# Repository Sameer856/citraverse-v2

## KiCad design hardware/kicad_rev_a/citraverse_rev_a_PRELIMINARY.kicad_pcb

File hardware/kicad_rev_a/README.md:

# Citraverse Rev A — preliminary KiCad interface and placement project

This is an editable KiCad 10 starting project based on the user's circular-board sketch. It is **not a fabrication-ready PCB**: there are no routed traces or implemented regulator/load-switch circuits. The board is now an 80 mm diameter placement to provide clearance for the full-size microSD socket, ESP32 antenna, radar, USB-C, microphone, speaker connector, and factory pads.

Open `citraverse_rev_a_PRELIMINARY.kicad_pro` in KiCad, then open its PCB or schematic. `preview/pcb-placement.png` and `preview/schematic.png` provide views without needing KiCad. The main project contains four copper layers and a 1.6 mm nominal thickness; stack-up and controlled-impedance requirements remain to be agreed with the fabricator.

## Implemented for review

- ESP32-S3-WROOM-1 footprint at the upper edge with antenna overhang and an all-copper-layer keepout reservation. The module pad numbering is sourced from the installed KiCad official ESP32-S3-WROOM-1 symbol. GPIO35–37 are not allocated on the N16R8.
- Centered MRS6240-P2512 footprint derived from the supplied guide's Figure 7-2: 12.00 × 25.00 mm body, 16 plated-through holes in two rows, 1.27 mm pitch, 0.90 × 2.15 mm pads, and 0.65 mm drill. The schematic records the 16 pin names/numbers. Check it against the physical purchased module before ordering any PCB.
- Left microSD socket, proposed Hirose DM3AT-SF-PEJM5 footprint, on its independent SPI bus. The card-detect contacts 9/10 are reserved and not yet used; the shield is `SH`.
- Right HRO TYPE-C-31-M-12 USB-C connector, native USB signal nets and separate 5.1 kΩ CC resistors. Connector sourcing and mechanical fit require confirmation.
- Common six-pin INMP441 breakout-module connector: VDD, GND, L/R, SD, WS, SCK. It retains the 100 nF local VDD bypass, 1 uF bulk bypass, 100 kΩ SD pulldown, and L/R grounded for left-channel operation. Verify the purchased module's printed header order before assembly; inexpensive breakouts occasionally change silkscreen order.
- MAX98357A I2S Class-D amplifier footprint and a two-pin JST-PH speaker connector. The speaker connector is differential (`SPK+`, `SPK-`); neither pin is ground.
- ESP enable pull-up/RC, service boot pull-up, local bypass placeholders and factory recovery connector.
- Four M2.5 mounting-hole candidates. Their placement must be reconciled with the enclosure, acoustic opening and antenna field of view.
- Native schematic connectivity and PCB net names, exported netlist, machine-readable pin contract and a reproducible generation script.

UART nets are explicitly named at the radar-module end: ESP GPIO18 drives `RADAR_RX_AT_MODULE` / radar PB1; ESP GPIO21 receives `RADAR_TX_AT_MODULE` / radar PB0. Radar SPI is reserved on GPIO10/12/11/13, optional lines 9/14; SD SPI is GPIO4/5/7/6; microphone I2S is GPIO15/16/17. GPIO8 is reserved for radar power enable. GPIO47 is only a PA11 reservation; it is not a confirmed data-ready signal.

## Work still required before a working board

1. Check the guide-derived MRS6240-P2512 and INMP441 footprints against physical parts. Confirm SPI role, electrical levels, reset timing, boot requirements and PA11/PA6 behavior with the dev kit/application firmware.
2. Replace `PS1` with a completed, reviewed USB-C power tree: input fuse and TVS, reverse-current protection, a 5 V protected rail for the speaker amplifier, a 3.3 V / 3 A buck for ESP32/SD/mic, and a separately switched 3.3 V radar rail. Prevent back-powering the unpowered radar through its signal pins.
3. Complete the native USB CDC factory-recovery circuit: USB ESD protection, 22 Ω D+/D- series resistors, EN/BOOT reset network, and labelled six-pad factory pogo access for 3V3/GND/EN/BOOT/UART TX/UART RX. A CH340/CP2102 bridge is deliberately not yet placed; native ESP32-S3 USB is the preferred primary factory/OTA path.
4. Complete SD pull-ups, radar series links/decoupling/reset network, USB protection and signal conditioning, status LED and temperature sensing. `STATUS_LED` and `BOARD_NTC` are only reserved MCU nets today.
5. Finalize purchased part numbers; review schematic electrical rules, pin directions and unconnected pins. The current custom block symbols are interface documentation, not a complete electrical schematic. Abstract power/radar pin types cannot validate electrical safety.
6. Keep the 80 mm round PCB, or redesign the SD location before attempting a 70 mm version. Then route the complete board, plan return paths and power planes, verify radio/microphone keepouts and USB geometry, then pass native ERC/DRC and manually review manufacturing outputs. No fabrication files have been generated.
7. Assemble and measure current, transients, heat and data throughput; complete the previously agreed combined-load and fault-injection tests.

## Validation performed

KiCad 10.0.3 successfully loaded and exported the PCB to SVG, and loaded/exported the schematic to SVG and a connectivity netlist. Both previews were visually inspected. The preliminary project has zero routed tracks by design. The KiCad command-line PCB DRC process aborted with exit 134 in this environment and did not produce a DRC report; **no DRC pass is claimed**. The host also emits font-cache warnings during schematic export, but generates the output files.

The generator overwrites these generated project files. After manual KiCad editing, preserve the edited project before re-running it. Run using KiCad's bundled Python, which supplies `pcbnew`:

```sh
/Applications/KiCad/KiCad.app/Contents/Frameworks/Python.framework/Versions/3.9/bin/python3 hardware/kicad_rev_a/build_preliminary.py
```

The reference drawing is the user's `IMG_9340.HEIC`. Design context is in the existing project architecture, module-review and ESP32 reliability documents. Their unresolved module/interface assumptions remain unresolved here.

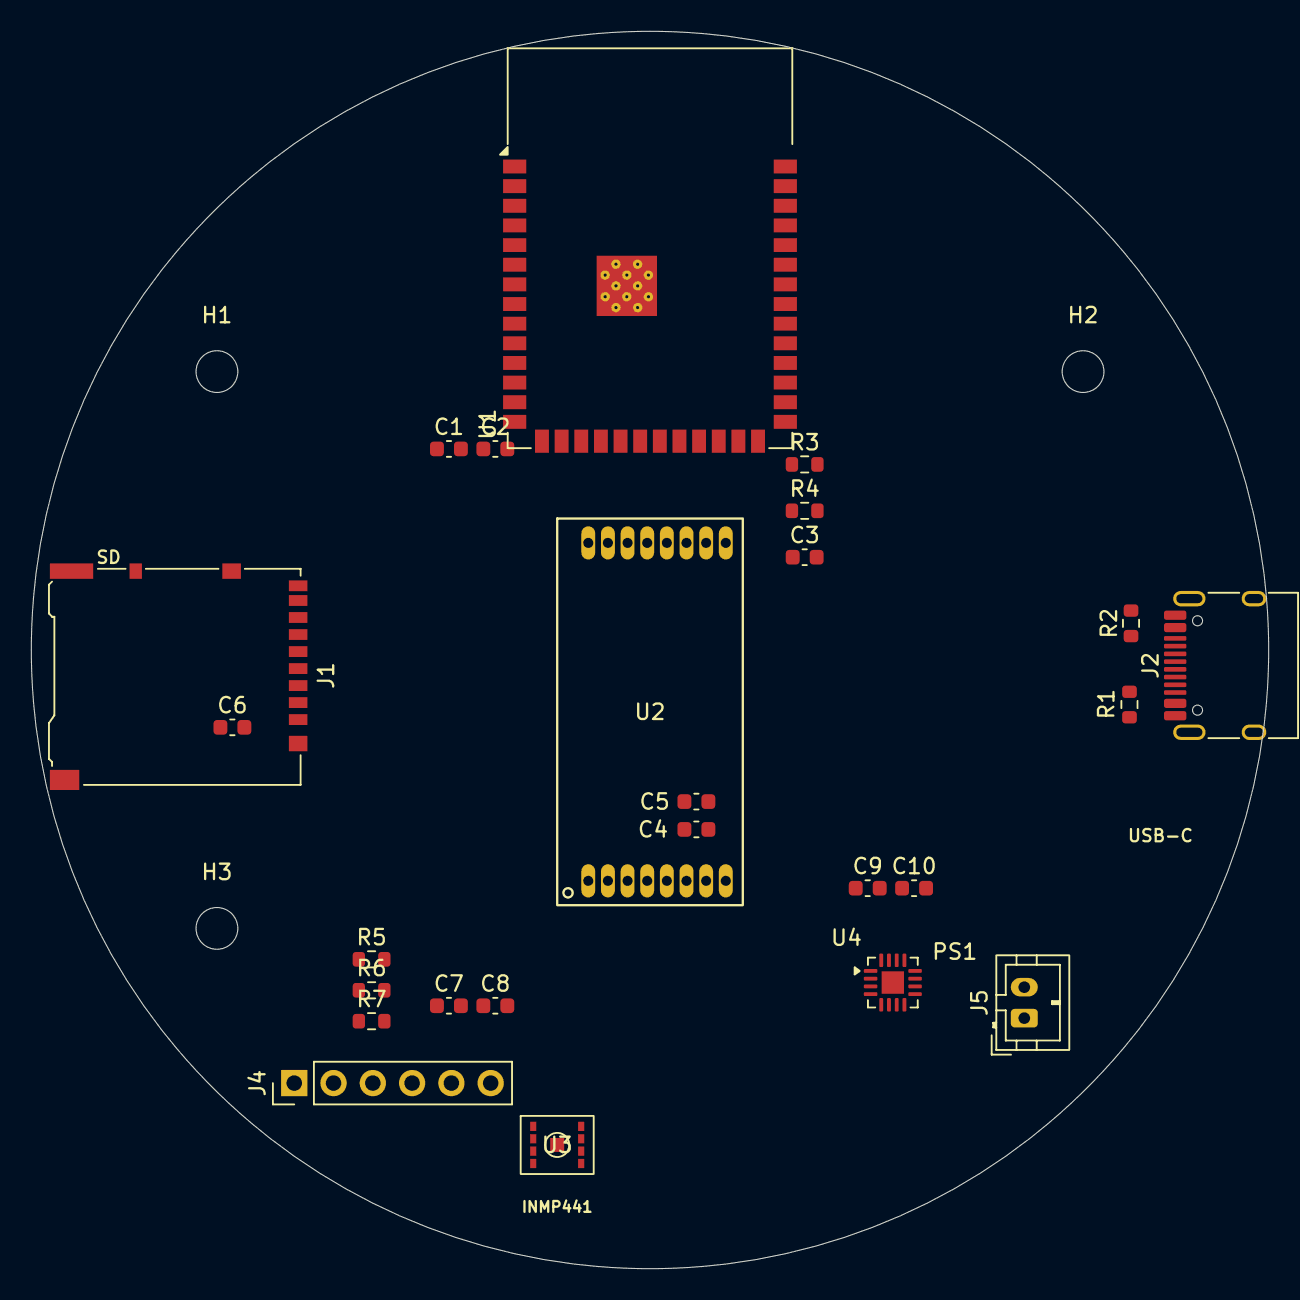
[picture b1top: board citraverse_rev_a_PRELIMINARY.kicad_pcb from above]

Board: 4 copper layers, 80.0 x 80.0 mm, 29 parts (0 on the bottom side), 31 nets, no tracks yet.

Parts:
C1: 10uF ESP32 bulk; C_0603_1608Metric
C2: 100nF ESP32 local; C_0603_1608Metric
C3: 1uF EN delay; C_0603_1608Metric
C4: 100nF radar local; C_0603_1608Metric
C5: 10uF radar bulk; C_0603_1608Metric
C6: 100nF SD local; C_0603_1608Metric
C7: 100nF INMP441 VDD; C_0603_1608Metric
C8: 1uF INMP441 bulk; C_0603_1608Metric
C9: 10uF speaker amp bulk; C_0603_1608Metric
C10: 100nF speaker amp local; C_0603_1608Metric
H1, H2, H3: MountingHole_2.7mm_M2.5
J1: microSD Hirose DM3AT-SF-PEJM5 candidate; microSD_HC_Hirose_DM3AT-SF-PEJM5
J2: USB-C 5V input / native USB; USB_C_Receptacle_HRO_TYPE-C-31-M-12
J4: Factory pogo: GND 3V3 EN BOOT TX RX; PinHeader_1x06_P2.54mm_Vertical
J5: JST-PH speaker output (from MAX98357A); JST_PH_B2B-PH-K_1x02_P2.00mm_Vertical
PS1: POWER BLOCK UNDESIGNED 5V to 3V3 >=2A
R1: 5.1k USB-C CC1; R_0603_1608Metric
R2: 5.1k USB-C CC2; R_0603_1608Metric
R3: 10k EN pull-up; R_0603_1608Metric
R4: 10k BOOT pull-up; R_0603_1608Metric
R5: 100k INMP441 SD pulldown; R_0603_1608Metric
R6: 0R INMP441 left select; R_0603_1608Metric
R7: 10k INMP441 enable; R_0603_1608Metric
U1: ESP32-S3-WROOM-1-N16R8; ESP32-S3-WROOM-1
U2: MRS6240-P2512 - guide-derived 16-pin THT footprint
U3: INMP441ACEZ-R7 bare bottom-port I2S microphone
U4: MAX98357AETE+ I2S Class-D speaker amplifier; QFN-16-1EP_3x3mm_P0.5mm_EP1.45x1.45mm

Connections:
3V3: C1.1, C2.1, C6.1, C7.1, C8.1, J1.4, J4.2, R3.2, R4.2, R5.2, R6.2, R7.1, R7.2, U1.2, U3.7, U3.8, U4.16
5V_PROTECTED: C9.1, C10.1, U4.7, U4.8
BOOT_SERVICE: J4.4, R4.1, U1.27
ESP_EN: C3.1, J4.3, R3.1, U1.3
GND: C1.2, C2.2, C3.2, C4.2, C5.2, C6.2, C7.2, C8.2, C9.2, C10.2, J1.6, J1.SH, J2.A1, J2.A12, J2.B1, J2.B12, J4.1, R1.2, R2.2, R6.1, U1.1, U1.40, U1.41, U2.6, U2.15, U3.4, U3.5, U3.6, U3.9, U4.2, U4.5, U4.11
I2S_BCLK: U1.8, U3.1, U4.6
I2S_WS: U1.9, U3.3, U4.4
MIC_DOUT: R5.1, U1.10, U3.2
RADAR_3V3: C4.1, C5.1, U2.7, U2.8
RADAR_CLK: U1.20, U2.13
RADAR_CS: U1.18, U2.14
RADAR_MISO: U1.21, U2.11
RADAR_MOSI: U1.19, U2.12
RADAR_NRST: U1.25, U2.5
RADAR_PA4: U1.22, U2.10
RADAR_PA5: U1.17, U2.9
RADAR_PA11_RESERVED: U1.24, U2.1
RADAR_RX_AT_MODULE: U1.11, U2.3
RADAR_TX_AT_MODULE: U1.23, U2.4
SD_CLK: J1.5, U1.5
SD_CS: J1.2, U1.4
SD_MISO: J1.7, U1.6
SD_MOSI: J1.3, U1.7
SPK_DIN: U1.38, U4.1
SPK_N: J5.2, U4.3
SPK_P: J5.1, U4.9
USB_5V: J2.A4, J2.A9, J2.B4, J2.B9
USB_CC1: J2.A5, R1.1
USB_CC2: J2.B5, R2.1
USB_D+: J2.A6, J2.B6
USB_D-: J2.A7, J2.B7

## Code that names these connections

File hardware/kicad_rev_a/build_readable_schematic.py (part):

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    ("U1", "ESP32-S3-WROOM-1-N16R8", 105, 125, [
        ("3V3", "1", "power_in", "3V3"), ("GND", "2", "power_in", "GND"), ("EN", "3", "input", "ESP_EN"),
        ("USB_D-", "4", "bidirectional", "USB_D-"), ("USB_D+", "5", "bidirectional", "USB_D+"),
        ("GPIO0 / BOOT", "6", "input", "BOOT_SERVICE"), ("GPIO10 / RADAR_CS", "7", "output", "RADAR_CS"),
        ("GPIO12 / RADAR_CLK", "8", "output", "RADAR_CLK"), ("GPIO11 / RADAR_MOSI", "9", "output", "RADAR_MOSI"),
        ("GPIO13 / RADAR_MISO", "10", "input", "RADAR_MISO"), ("GPIO7 / RADAR_NOTIFY", "11", "input", "RADAR_NOTIFY"),
        ("GPIO9 / RADAR_NRST", "12", "output", "RADAR_NRST"), ("GPIO8 / RADAR_UPD", "13", "output", "RADAR_UPD"),
        ("GPIO18 / RADAR_UART_RX", "14", "input", "RADAR_UART_TX"), ("GPIO17 / RADAR_UART_TX", "15", "output", "RADAR_UART_RX"),
        ("GPIO4 / I2S_WS", "16", "output", "I2S_WS"), ("GPIO5 / I2S_BCLK", "17", "output", "I2S_BCLK"),
        ("GPIO6 / MIC_DOUT", "18", "input", "MIC_DOUT"), ("GPIO21 / SD_CS", "19", "output", "SD_CS"),
        ("GPIO14 / SD_SCLK", "20", "output", "SD_SCLK"), ("GPIO15 / SD_MISO", "21", "input", "SD_MISO"),
        ("GPIO16 / SD_MOSI", "22", "output", "SD_MOSI"), ("GPIO19 / RADAR_POWER_EN", "23", "output", "RADAR_POWER_EN")]),
    ("U2", "MRS6240-P2512 60 GHz radar", 205, 118, [
        ("VCC", "7", "power_in", "RADAR_3V3"), ("VDDIO", "8", "power_in", "RADAR_3V3"),
        ("GND", "6", "power_in", "GND"), ("GND", "15", "power_in", "GND"),
        ("PA0 / CS", "14", "input", "RADAR_CS"), ("PA1 / CLK", "13", "input", "RADAR_CLK"),
        ("PA2 / MOSI", "12", "input", "RADAR_MOSI"), ("PA3 / MISO", "11", "output", "RADAR_MISO"),
        ("PA6 / Notify", "2", "output", "RADAR_NOTIFY"), ("PB0 / UART TX / UPD", "4", "output", "RADAR_UART_TX"),
        ("PB1 / UART RX", "3", "input", "RADAR_UART_RX"), ("NRST", "5", "input", "RADAR_NRST")]),
    ("J2", "microSD socket — SPI3", 190, 170, [
        ("VDD", "4", "power_in", "3V3"), ("VSS", "6", "power_in", "GND"), ("CS", "2", "input", "SD_CS"),
        ("SCLK", "5", "input", "SD_SCLK"), ("MOSI", "3", "input", "SD_MOSI"), ("MISO", "7", "output", "SD_MISO")]),
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
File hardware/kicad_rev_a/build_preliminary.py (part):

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sdnames=['DAT2_NC','DAT3_CS','CMD_MOSI','VDD','CLK','VSS','DAT0_MISO','DAT1_NC','SWITCH_1_RESERVED','SWITCH_2_RESERVED']
add('J1','microSD Hirose DM3AT-SF-PEJM5 candidate','Connector_Card:microSD_HC_Hirose_DM3AT-SF-PEJM5',[(str(i+1),n,'passive') for i,n in enumerate(sdnames)]+[('SH','SHIELD','passive')],{'2':'SD_CS','3':'SD_MOSI','4':'3V3','5':'SD_CLK','6':'GND','7':'SD_MISO','SH':'GND'},(170,115),(73,109),-90)
usbpins=[(n,s,'passive') for n,s in [('A1','GND'),('A4','VBUS'),('A5','CC1'),('A6','D+'),('A7','D-'),('A8','SBU1'),('A9','VBUS'),('A12','GND'),('B1','GND'),('B4','VBUS'),('B5','CC2'),('B6','D+'),('B7','D-'),('B8','SBU2'),('B9','VBUS'),('B12','GND'),('S1','SHIELD')]]
usbnet={n:({'GND':'GND','VBUS':'USB_5V','CC1':'USB_CC1','CC2':'USB_CC2','D+':'USB_D+','D-':'USB_D-','SHIELD':'GND'}.get(s)) for n,s,_ in usbpins}
usbnet={n:v for n,v in usbnet.items() if v}
add('J2','USB-C 5V input / native USB','Connector_USB:USB_C_Receptacle_HRO_TYPE-C-31-M-12',usbpins,usbnet,(280,58),(138,101),90)
# Common six-pin breakout module, viewed at its connector: VDD, GND, L/R, SD, WS, SCK.
micpins=[('1','VDD','power_in'),('2','GND','power_in'),('3','L_R','input'),('4','SD','output'),('5','WS','input'),('6','SCK','input')]
add('U3','INMP441 6-pin breakout module','Connector_PinHeader_2.54mm:PinHeader_1x06_P2.54mm_Vertical',micpins,{'1':'3V3','2':'GND','3':'GND','4':'MIC_DOUT','5':'I2S_WS','6':'I2S_BCLK'},(170,158),(94,132),90)
powerpins=[('1','USB_5V_IN','passive'),('2','3V3_MAIN_OUT','passive'),('3','GND','passive'),('4','RADAR_ENABLE','passive'),('5','RADAR_3V3_OUT','passive')]
add('PS1','POWER BLOCK UNDESIGNED 5V to 3V3 >=2A','Citraverse:POWER_UNDESIGNED_NO_PADS',powerpins,{'1':'USB_5V','2':'3V3','3':'GND','4':'RADAR_POWER_EN','5':'RADAR_3V3'},(280,112),(125,117))
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    other='GND' if ref in ['R1','R2'] else '3V3'
    add(ref,val,'Resistor_SMD:R_0603_1608Metric',[('1','1','passive'),('2','2','passive')],{'1':net,'2':other},spos,bpos)
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    add(ref,val,'Capacitor_SMD:C_0603_1608Metric',[('1','1','passive'),('2','2','passive')],{'1':net,'2':'GND'},spos,bpos)
service=[('1','GND','passive'),('2','3V3','passive'),('3','EN','passive'),('4','BOOT','passive'),('5','UART_TX','passive'),('6','UART_RX','passive')]
add('J4','Factory pogo: GND 3V3 EN BOOT TX RX','Connector_PinHeader_2.54mm:PinHeader_1x06_P2.54mm_Vertical',service,{'1':'GND','2':'3V3','3':'ESP_EN','4':'BOOT_SERVICE','5':'FACTORY_UART_TX','6':'FACTORY_UART_RX'},(170,203),(77,128),90)
speakerpins=[('1','SPK+','passive'),('2','SPK-','passive')]
add('J5','JST-PH speaker output (from MAX98357A)','Connector_JST:JST_PH_B2B-PH-K_1x02_P2.00mm_Vertical',speakerpins,{'1':'SPK_P','2':'SPK_N'},(230,203),(122,124),180)
amppins=[(str(n),name,'passive') for n,name in [(1,'DIN'),(2,'GAIN_SLOT'),(3,'OUTN'),(4,'LRCLK'),(5,'GND'),(6,'BCLK'),(7,'VDD'),(8,'VDD'),(9,'OUTP'),(10,'NC'),(11,'GND'),(12,'NC'),(13,'NC'),(14,'NC'),(15,'NC'),(16,'SD_MODE'),('EP','EP_GND')]]
add('U4','MAX98357AETE+ I2S Class-D speaker amplifier','Package_DFN_QFN:QFN-16-1EP_3x3mm_P0.5mm_EP1.45x1.45mm',amppins,{'1':'SPK_DIN','2':'GND','3':'SPK_N','4':'I2S_WS','5':'GND','6':'I2S_BCLK','7':'5V_PROTECTED','8':'5V_PROTECTED','9':'SPK_P','11':'GND','16':'3V3','EP':'GND'},(230,160),(121,119))

board=p.BOARD(); board.SetCopperLayerCount(4)
board.GetDesignSettings().SetBoardThickness(p.FromMM(1.6))
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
